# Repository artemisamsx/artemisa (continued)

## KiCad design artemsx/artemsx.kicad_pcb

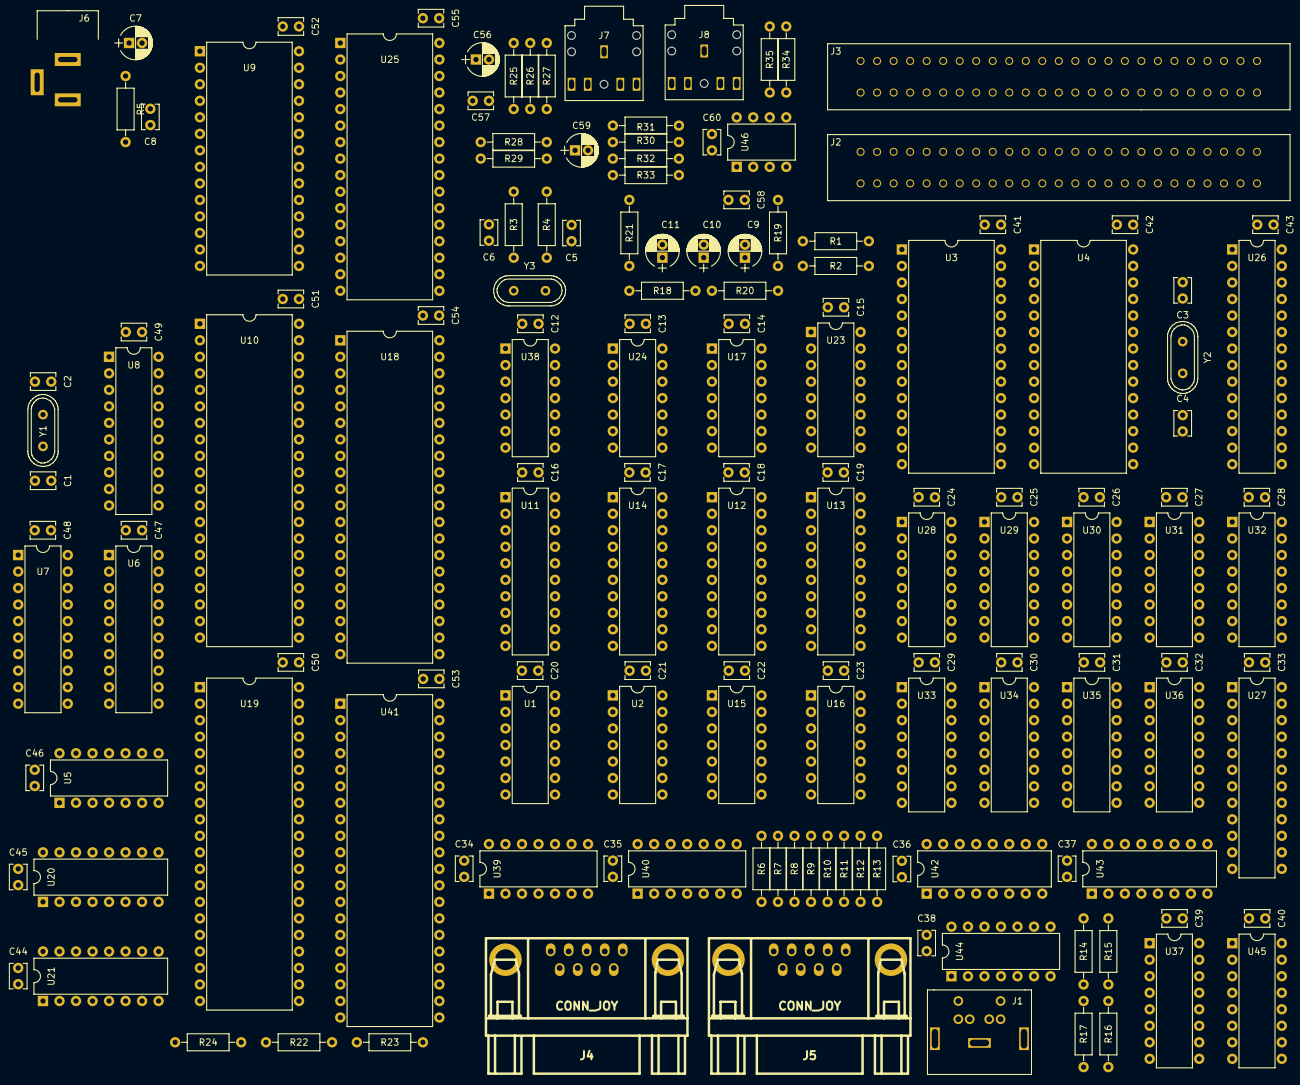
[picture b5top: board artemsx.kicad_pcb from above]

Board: 2 copper layers, 151 parts (0 on the bottom side), 249 nets, no tracks yet.

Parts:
C1, C2: 27pF; Disc_capacitor
C3, C4, C5, C6, C8, C12, C13, C14, C15, C16, C17, C18, C19, C20, C21, C22, C23, C24, C25, C26, C27, C28, C29, C30, C31, C32, C33, C34, C35, C36, C37, C38, C39, C40, C41, C42, C43, C44, C45, C46, C47, C48, C49, C50, C51, C52, C53, C54, C55, C60: 22pF; Disc_capacitor
C7, C56, C59: 1uF; Radial_capacitor
C9, C10, C11: 10u; Radial_capacitor
C57, C58: 22nF; Disc_capacitor
J1: PS2_CONN; PS2_conn
J2, J3: MSX_Slot; Slot_conn
J4, J5: CONN_JOY; Joystick_conn
J6: PWR_conn; Jack_55_21
J7, J8: Audio_conn; Jack_conn
R1, R2, R5, R6, R7, R8, R9, R10, R11, R12, R13, R14, R15, R16, R17, R22, R23, R24: 10K; Axial_resistor
R3: 1M; Axial_resistor
R4: 1K; Axial_resistor
R18: 470; Axial_resistor
R19: 20k; Axial_resistor
R20, R25, R26, R31: 4k7; Axial_resistor
R21, R28, R29: 2k7; Axial_resistor
R27: 100; Axial_resistor
R30, R34: 10k; Axial_resistor
R32: 220k; Axial_resistor
R33: 1k; Axial_resistor
R35: 470k; Axial_resistor
U1, U17, U24, U44: 74HC32; DIP-14_300
U2: 74HC04; DIP-14_300
U3, U4, U9: HM62256ALP-10; DIP-28_600
U5: 74HCT04; DIP-14_300
U6, U7, U8: 74HCT574; DIP-20_300
U10: TMS99x8; DIP-40_600
U11, U12, U14: 74HCT244; DIP-20_300
U13: 74HCT245; DIP-20_300
U15, U40: 74HC74; DIP-14_300
U16: 74HC08; DIP-14_300
U18: Z84C00; DIP-40_600
U19: 82C55A; DIP-40_600
U20: 74HC153; DIP-16_300
U21: 74HC139; DIP-16_300
U23: 74HC138; DIP-16_300
U25: SST39SF0x0; DIP-32_600
U26: ATMEGA328P; DIP-28_300
U27: 74HC154; DIP-24_300
U28, U29, U30, U31, U32, U33, U34, U35, U36, U37, U45: 74HC595; DIP-16_300
U38: 4069; DIP-14_300
U39: 74HC07; DIP-14_300
U41: AY-3-8910; DIP-40_600
U42, U43: 74HC157; DIP-16_300
U46: LM311; DIP-8_300
Y1: 10.7386Mhz; Crystal
Y2: 16Mhz; Crystal
Y3: 3.58Mhz; Crystal

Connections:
/ADDR0: J2.28, J3.28, U3.10, U4.10, U10.13, U11.18, U24.12, U25.12
/ADDR1: J2.27, J3.27, U3.9, U4.9, U11.16, U25.11, U38.13, U44.2
/ADDR3: J2.29, J3.29, U3.7, U4.7, U11.12, U23.1, U25.9
/ADDR4: J2.32, J3.32, U3.6, U4.6, U11.9, U23.2, U25.8
/ADDR5: J2.31, J3.31, U3.5, U4.5, U11.7, U23.3, U25.7
/ADDR6: J2.22, J3.22, U3.4, U4.4, U11.5, U24.2, U25.6
/ADDR7: J2.21, J3.21, U2.9, U3.3, U4.3, U11.3, U25.5
/ADDR14: J2.25, J3.25, U3.1, U4.1, U12.5, U19.9, U20.14, U21.14, U25.29
/ADDR15: J2.18, J3.18, U1.2, U2.1, U12.3, U19.8, U20.2, U21.13, U25.3
/AUDIO: R19.2, R20.2, R21.2
/BEEP: C9.1, U19.10
/CASIN: C58.2, U41.14
/CASOUT: C56.1, U19.12
/CLK: U2.12, U15.3, U15.11, U18.6, U40.3, U44.9, U44.10
/CPU/A0: U11.2, U18.30
/CPU/A1: U11.4, U18.31
/CPU/A2: U11.6, U18.32
/CPU/A3: U11.8, U18.33
/CPU/A4: U11.11, U18.34
/CPU/A5: U11.13, U18.35
/CPU/A6: U11.15, U18.36
/CPU/A7: U11.17, U18.37
/CPU/A8: U12.2, U18.38
/CPU/A9: U12.4, U18.39
/CPU/A10: U12.6, U18.40
/CPU/A11: U12.8, U18.1
/CPU/A12: U12.11, U18.2
/CPU/A13: U12.13, U18.3
/CPU/A14: U12.15, U18.4
/CPU/A15: U12.17, U18.5
/CPU/ADDR2: J2.30, J3.30, U3.8, U4.8, U11.14, U25.10
/CPU/ADDR8: J2.24, J3.24, U3.25, U4.25, U12.18, U25.27
/CPU/ADDR9: J2.17, J3.17, U3.24, U4.24, U12.16, U25.26
/CPU/ADDR10: J2.20, J3.20, U3.21, U4.21, U12.14, U25.23
/CPU/ADDR11: J2.19, J3.19, U3.23, U4.23, U12.12, U25.25
/CPU/ADDR12: J2.23, J3.23, U3.2, U4.2, U12.9, U25.4
/CPU/ADDR13: J2.26, J3.26, U3.26, U4.26, U12.7, U25.28
/CPU/D0: U13.2, U18.14
/CPU/D1: U13.3, U18.15
/CPU/D2: U13.4, U18.12
/CPU/D3: U13.5, U18.8
/CPU/D4: U13.6, U18.7
/CPU/D5: U13.7, U18.9
/CPU/D6: U13.8, U18.10
/CPU/D7: U13.9, U18.13
/CPU/DATA0: J2.34, J3.34, U3.11, U4.11, U10.24, U13.18, U19.34, U25.13, U41.37
/CPU/DATA1: J2.33, J3.33, U3.12, U4.12, U10.23, U13.17, U19.33, U25.14, U41.36
/CPU/DATA2: J2.36, J3.36, U3.13, U4.13, U10.22, U13.16, U19.32, U25.15, U41.35
/CPU/DATA3: J2.35, J3.35, U3.15, U4.15, U10.21, U13.15, U19.31, U25.17, U41.34
/CPU/DATA4: J2.38, J3.38, U3.16, U4.16, U10.20, U13.14, U19.30, U25.18, U41.33
/CPU/DATA5: J2.37, J3.37, U3.17, U4.17, U10.19, U13.13, U19.29, U25.19, U41.32
/CPU/DATA6: J2.40, J3.40, U3.18, U4.18, U10.18, U13.12, U19.28, U25.20, U41.31
/CPU/DATA7: J2.39, J3.39, U3.19, U4.19, U10.17, U13.11, U19.27, U25.21, U41.30
/CPU/~INT: U16.3, U18.16
/KBD/DS: U26.11, U28.14, U29.14, U30.14, U31.14, U32.14, U33.14, U34.14, U35.14, U36.14, U37.14, U45.14
/KBD/KBCOL0: U19.18, U28.15, U29.15, U30.15, U31.15, U32.15, U33.15, U34.15, U35.15, U36.15, U37.15, U45.15
/KBD/KBCOL1: U19.19, U28.1, U29.1, U30.1, U31.1, U32.1, U33.1, U34.1, U35.1, U36.1, U37.1, U45.1
/KBD/KBCOL2: U19.20, U28.2, U29.2, U30.2, U31.2, U32.2, U33.2, U34.2, U35.2, U36.2, U37.2, U45.2
/KBD/KBCOL3: U19.21, U28.3, U29.3, U30.3, U31.3, U32.3, U33.3, U34.3, U35.3, U36.3, U37.3, U45.3
/KBD/KBCOL4: U19.22, U28.4, U29.4, U30.4, U31.4, U32.4, U33.4, U34.4, U35.4, U36.4, U37.4, U45.4
/KBD/KBCOL5: U19.23, U28.5, U29.5, U30.5, U31.5, U32.5, U33.5, U34.5, U35.5, U36.5, U37.5, U45.5
/KBD/KBCOL6: U19.24, U28.6, U29.6, U30.6, U31.6, U32.6, U33.6, U34.6, U35.6, U36.6, U37.6, U45.6
/KBD/KBCOL7: U19.25, U28.7, U29.7, U30.7, U31.7, U32.7, U33.7, U34.7, U35.7, U36.7, U37.7, U45.7
/KBD/KBROW0: U19.14, U27.23
/KBD/KBROW1: U19.15, U27.22
/KBD/KBROW2: U19.16, U27.21
/KBD/KBROW3: U19.17, U27.20
/KBD/SHCP: U26.6, U28.11, U29.11, U30.11, U31.11, U32.11, U33.11, U34.11, U35.11, U36.11, U37.11, U45.11
/KBD/STCP0: U26.23, U28.12
/KBD/STCP1: U26.24, U29.12
/KBD/STCP2: U26.25, U30.12
/KBD/STCP3: U26.26, U31.12
/KBD/STCP4: U26.27, U32.12
/KBD/STCP5: U26.28, U33.12
/KBD/STCP6: U26.14, U34.12
/KBD/STCP7: U26.15, U35.12
/KBD/STCP8: U26.16, U36.12
/KBD/STCP9: U26.17, U37.12
/KBD/STCP10: U26.18, U45.12
/KBD/~RSL0: U27.1, U28.13
/KBD/~RSL1: U27.2, U29.13
/KBD/~RSL2: U27.3, U30.13
/KBD/~RSL3: U27.4, U31.13
/KBD/~RSL4: U27.5, U32.13
/KBD/~RSL5: U27.6, U33.13
/KBD/~RSL6: U27.7, U34.13
/KBD/~RSL7: U27.8, U35.13
/KBD/~RSL8: U27.9, U36.13
/KBD/~RSL9: U27.10, U37.13
/KBD/~RSL10: U27.11, U45.13
/PPI/PA0: U19.4, U20.6
/PPI/PA1: U19.3, U20.10
/PPI/PA2: U19.2, U20.5
/PPI/PA3: U19.1, U20.11
/PPI/PA4: U19.40, U20.4
/PPI/PA5: U19.39, U20.12
/PPI/PA6: U19.38, U20.3
/PPI/PA7: U19.37, U20.13
/PSG/IOA0: U41.21, U42.4
/PSG/IOA1: U41.20, U42.7
/PSG/IOA2: U41.19, U42.9
/PSG/IOA3: U41.18, U42.12
/PSG/IOA4: U41.17, U43.4
/PSG/IOA5: U41.16, U43.7
/PSG/IOB0: U39.1, U41.13
/PSG/IOB1: U39.3, U41.12
/PSG/IOB2: U39.5, U41.11
/PSG/IOB3: U39.9, U41.10
/PSG/IOB4: J4.8, U41.9
/PSG/IOB5: J5.8, U41.8
/PSG/IOB6: U41.7, U42.1, U43.1
/PSG/JOYA1: J4.1, R13.2, U42.2
/PSG/JOYA2: J4.2, R12.2, U42.5
/PSG/JOYA3: J4.3, R11.2, U42.11
/PSG/JOYA4: J4.4, R10.2, U42.14
/PSG/JOYA6: J4.6, R17.1, U39.8, U43.2
/PSG/JOYA7: J4.7, R16.1, U39.6, U43.5
/PSG/JOYB1: J5.1, R9.2, U42.3
/PSG/JOYB2: J5.2, R8.2, U42.6
/PSG/JOYB3: J5.3, R7.2, U42.10
/PSG/JOYB4: J5.4, R6.2, U42.13
/PSG/JOYB6: J5.6, R15.1, U39.4, U43.3
/PSG/JOYB7: J5.7, R14.1, U39.2, U43.6
/SLOTS/EXTCLK: J2.42, J3.42, U44.8
/SLOTS/~EXTRESET: J2.15, J3.15, U44.11
/SOUND: C10.1, J2.49, J3.49
/VDP/AD0: U6.2, U7.2, U8.2, U10.10
/VDP/AD1: U6.3, U7.3, U8.3, U10.9
/VDP/AD2: U6.4, U7.4, U8.4, U10.8
/VDP/AD3: U6.5, U7.5, U8.5, U10.7
/VDP/AD4: U6.6, U7.6, U8.6, U10.6
/VDP/AD5: U6.7, U7.7, U8.7, U10.5
/VDP/AD6: U6.8, U7.8, U8.8, U10.4
/VDP/AD7: U6.9, U7.9, U8.9, U10.3
/VDP/COL: U5.12, U8.11
/VDP/RD: U5.4, U6.1, U9.27
/VDP/ROW: U5.6, U7.11
/VDP/VD0: U6.19, U9.11, U10.32
/VDP/VD1: U6.18, U9.12, U10.31
/VDP/VD2: U6.17, U9.13, U10.30
/VDP/VD3: U6.16, U9.15, U10.29
/VDP/VD4: U6.15, U9.16, U10.28
/VDP/VD5: U6.14, U9.17, U10.27
/VDP/VD6: U6.13, U9.18, U10.26
/VDP/VD7: U6.12, U9.19, U10.25
/VDP/WR: U5.2, U5.3, U6.11, U9.22
/VDP/~CAS: U5.9, U9.20, U10.2
/VDP/~CSR: U1.11, U10.15
/VDP/~CSW: U1.8, U10.14
/VDP/~RAS: U5.5, U10.1
/~CS1: J2.1, J3.1, U16.10, U21.11
/~CS2: J2.2, J3.2, U16.9, U21.10
/~CS12: J2.3, J3.3, U16.8
/~EXTINT: J2.8, J3.8, R1.2, U16.1
/~EXTWAIT: J2.7, J3.7, R2.2, U15.1, U15.10
/~IORQ: J2.11, J3.11, U14.14, U17.1, U23.5
/~IOSL3: U1.10, U1.12, U23.12
/~IOSL4: U23.11, U24.10, U44.1
/~IOSL5: U17.5, U17.9, U23.10, U40.10
/~M1: J2.9, J3.9, U14.18, U15.2, U17.2, U23.6
/~MREQ: J2.12, J3.12, U14.16, U17.12
/~RD: J2.14, J3.14, U1.13, U3.22, U4.22, U14.9, U16.4, U17.4, U21.15, U24.4, U25.24
/~RESET: C8.1, U2.3, U10.34, U18.26, U26.1, U38.4, U40.13, U41.23, U44.12, U44.13
/~RFSH: J2.6, J3.6, U2.5, U14.5
/~SLTSL0: U21.4, U25.22
/~SLTSL1: U1.1, U1.4, U21.5
/~SLTSL2: J2.4, U21.6
/~SLTSL3: J3.4, U21.7
/~VDPINT: U10.16, U16.2
/~WR: J2.13, J3.13, U1.9, U3.27, U4.27, U14.7, U17.10, U44.5
GND: C1.2, C2.2, C3.2, C4.2, C5.2, C6.2, C7.2, C8.2, C12.2, C13.2, C14.2, C15.2, C16.2, C17.2, C18.2, C19.2, C20.2, C21.2, C22.2, C23.2, C24.2, C25.2, C26.2, C27.2, C28.2, C29.2, C30.2, C31.2, C32.2, C33.2, C34.2, C35.2, C36.2, C37.2, C38.2, C39.2, C40.2, C41.2, C42.2, C43.2, C44.2, C45.2, C46.2, C47.2, C48.2, C49.2, C50.2, C51.2, C52.2, C53.2, C54.2, C55.2, C57.2, C59.2, C60.2, J1.3, J2.41, J2.43, J2.48, J2.50, J3.41, J3.43, J3.48, J3.50, J4.9, J5.9, J6.2, J6.3, J7.1, J8.1, R18.2, R22.2, R23.2, R24.1, R27.1, R29.1, U1.7, U2.7, U3.14, U4.14, U5.7, U6.10, U7.1, U7.10, U8.1, U8.10, U9.1, U9.14, U10.12, U11.1, U11.10, U11.19, U12.1, U12.10, U12.19, U13.10, U13.19, U14.1, U14.8, U14.10, U14.17, U14.19, U15.7, U16.7, U17.7, U18.29, U19.6, U19.7, U20.8, U21.8, U23.8, U24.7, U25.1, U25.2, U25.16, U25.30, U26.8, U26.22, U27.12, U27.18, U27.19, U28.8, U29.8, U30.8, U31.8, U32.8, U33.8, U34.8, U35.8, U36.8, U37.8, U38.7, U39.7, U40.7, U40.11, U40.12, U41.1, U41.24, U42.8, U42.15, U43.8, U43.10, U43.11, U43.13, U43.14, U43.15, U44.7, U45.8, U46.1, U46.4
unnamed: C1.1, U10.40, Y1.1
unnamed: C2.1, U10.39, Y1.2
unnamed: C3.1, U26.9, Y2.1
unnamed: C4.1, U26.10, Y2.2
unnamed: C5.1, R4.2, Y3.2
unnamed: C6.1, R3.2, U38.5, Y3.1
unnamed: C7.1, R5.2, U38.1
unnamed: C9.2, R19.1
unnamed: C10.2, R20.1
unnamed: C11.1, R18.1, U41.3, U41.4, U41.38
unnamed: C11.2, R21.1
unnamed: C56.2, R25.2
unnamed: C57.1, R25.1, R26.2
unnamed: C58.1, R34.1
unnamed: C59.1, R28.1, R29.2, R30.2, R31.1
unnamed: J1.1, U26.5
unnamed: J1.5, U26.4
unnamed: J7.2, R26.1, R27.2
unnamed: J8.2, R32.2, R33.1, U46.7
unnamed: R3.1, R4.1, U38.6, U38.9
unnamed: R22.1, U41.6
unnamed: R23.1, U41.15
unnamed: R30.1, R34.2, R35.1, U46.3
unnamed: R31.2, R32.1, U46.2
unnamed: U1.3, U3.20
unnamed: U1.5, U2.2
unnamed: U1.6, U4.20
unnamed: U2.8, U24.1
unnamed: U2.10, U41.29
unnamed: U2.13, U38.8
unnamed: U5.10, U5.13
unnamed: U5.8, U5.11
unnamed: U7.12, U9.4
unnamed: U7.13, U9.5
unnamed: U7.14, U9.6
unnamed: U7.15, U9.7
unnamed: U7.16, U9.8
unnamed: U7.17, U9.9
unnamed: U7.18, U9.10
unnamed: U8.12, U9.26
unnamed: U8.13, U9.2
unnamed: U8.14, U9.23
unnamed: U8.15, U9.21
unnamed: U8.16, U9.24
unnamed: U8.17, U9.25
unnamed: U8.18, U9.3
unnamed: U5.1, U10.11
unnamed: U13.1, U16.6
unnamed: U14.2, U18.27
unnamed: U14.4, U18.19
unnamed: U14.6, U18.20
unnamed: U14.11, U18.21
unnamed: U14.13, U18.22
unnamed: U14.15, U18.28
unnamed: U15.4, U15.9
unnamed: U15.5, U15.12, U18.24
unnamed: U16.5, U17.3
unnamed: U2.11, U16.11
unnamed: U16.12, U24.8
unnamed: U16.13, U24.11
unnamed: U17.6, U19.5
unnamed: U17.8, U19.36
unnamed: U17.11, U21.1
unnamed: U2.6, U17.13
unnamed: U2.4, U19.35
unnamed: U20.1, U20.15, U40.8
unnamed: U20.7, U21.2
unnamed: U20.9, U21.3
unnamed: U23.4, U24.3
unnamed: U24.5, U38.12
unnamed: U24.6, U24.9
unnamed: U24.13, U38.11, U44.6
unnamed: U38.2, U38.3
unnamed: U38.10, U41.27
unnamed: U40.2, U40.6
unnamed: U40.5, U41.22
unnamed: U44.3, U44.4
VCC: C12.1, C13.1, C14.1, C15.1, C16.1, C17.1, C18.1, C19.1, C20.1, C21.1, C22.1, C23.1, C24.1, C25.1, C26.1, C27.1, C28.1, C29.1, C30.1, C31.1, C32.1, C33.1, C34.1, C35.1, C36.1, C37.1, C38.1, C39.1, C40.1, C41.1, C42.1, C43.1, C44.1, C45.1, C46.1, C47.1, C48.1, C49.1, C50.1, C51.1, C52.1, C53.1, C54.1, C55.1, C60.1, J1.4, J2.45, J2.47, J3.45, J3.47, J4.5, J5.5, J6.1, R1.1, R2.1, R5.1, R6.1, R7.1, R8.1, R9.1, R10.1, R11.1, R12.1, R13.1, R14.2, R15.2, R16.2, R17.2, R28.2, R33.2, R35.2, U1.14, U2.14, U3.28, U4.28, U5.14, U6.20, U7.20, U8.20, U9.28, U10.33, U11.20, U12.20, U13.20, U14.20, U15.13, U15.14, U16.14, U17.14, U18.11, U18.17, U18.25, U19.26, U20.16, U21.16, U23.16, U24.14, U25.31, U25.32, U26.7, U26.20, U26.21, U27.24, U28.10, U28.16, U29.10, U29.16, U30.10, U30.16, U31.10, U31.16, U32.10, U32.16, U33.10, U33.16, U34.10, U34.16, U35.10, U35.16, U36.10, U36.16, U37.10, U37.16, U38.14, U39.11, U39.13, U39.14, U40.1, U40.4, U40.14, U41.25, U41.28, U41.40, U42.16, U43.16, U44.14, U45.10, U45.16, U46.8

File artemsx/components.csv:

Ref,Type,Sheet
U1A,74HC32,RAM
U1B,74HC32,RAM
U1C,74HC32,VDP
U1D,74HC32,VDP
U2A,74HC04,RAM
U2B,74HC04,PPI
U2C,74HC04,PPI
U2D,74HC04,IO
U2E,74HC04,PSG
U2F,74HC04,---
U3,HM62256ALP-10,RAM
U4,HM62256ALP-10,RAM
U5A,74HCT04,VDP
U5B,74HCT04,VDP
U5C,74HCT04,VDP
U5D,74HCT04,VDP
U5E,74HCT04,VDP
U5F,74HCT04,VDP
U6,74HCT574,VDP
U7,74HCT574,VDP
U8,74HCT574,VDP
U9,HM62256ALP-10,VDP
U10,TMS99x8,VDP
U11A,74HCT244,CPU
U11B,74HCT244,CPU
U12A,74HCT244,CPU
U12B,74HCT244,CPU
U13,74HCT245,CPU
U14A,74HCT244,CPU
U14B,74HCT244,CPU
U15A,74HC74,CPU
U15B,74HC74,CPU
U16A,74HC08,CPU
U16B,74HC08,CPU
U16C,74HC08,PPI
U16D,74HC08,PSG
U17A,74HC32,CPU
U17B,74HC32,PPI
U17C,74HC32,PPI
U17D,74HC32,PPI
U18,Z84C006,CPU
U19,82C55A,PPI
U20,74HC153,PPI
U21A,74HC139,PPI
U21B,74HC139,PPI
U23,74HC138,IO
U24A,74HC32,IO
U24B,74HC32,PSG
U24C,74HC32,PSG
U24D,74HC32,PSG
U25,SST39SF0x0,ROM
U26,ATMEGA328P,KBD
U27,74HC154,KBD
U28,74HC595,KBD
U29,74HC595,KBD
U30,74HC595,KBD
U31,74HC595,KBD
U32,74HC595,KBD
U33,74HC595,KBD
U34,74HC595,KBD
U35,74HC595,KBD
U36,74HC595,KBD
U37,74HC595,KBD
U38A,4069,CPU
U38B,4069,CPU
U38C,4069,CPU
U38D,4069,CPU
U38E,4069,PSG
U38F,4069,PSG
U39A,74HC07,PSG
U39B,74HC07,PSG
U39C,74HC07,PSG
U39D,74HC07,PSG
U39E,74HC07,PSG*
U39F,74HC07,PSG*
U40A,74HC74,PSG
U40B,74HC74,PPI
U41,AY-3-8910,PSG
U42,74HC157,PSG
U43,74HC157,PSG
U44A,74HC32,PSG
U44B,74HC32,PSG
U44C,74HC32,SLOTS
U44D,74HC32,SLOTS
U45,74HC595,KBD
U46,LM311,CAS
Y1,10.7386,VDP
Y2,16MHZ,KBD
Y3,3.58MHZ,CPU
R1,10K,SLOTS
R2,10K,SLOTS
R3,1M,CPU
R4,1K,CPU
R5,10K,CPU
R6,10K,PSG
R7,10K,PSG
R8,10K,PSG
R9,10K,PSG
R10,10K,PSG
R11,10K,PSG
R12,10K,PSG
R13,10K,PSG
R14,10K,PSG
R15,10K,PSG
R16,10K,PSG
R17,10K,PSG
R18,470,PSG
R19,20k,PSG
R20,4k7,PSG
R21,2k7,PSG
R22,10K,PSG
R23,10K,PSG
R24,10K,PSG
R25,4k7,CAS
R26,4k7,CAS
R27,100,CAS
R28,2k7,CAS
R29,2k7,CAS
R30,10k,CAS
R31,4k7,CAS
R32,220k,CAS
R33,1k,CAS
R34,10k,CAS
R35,470k,CAS
J1,PS2CONN,KBD
J2,MSXSLOT,SLOTS
J3,MSXSLOT,SLOTS
J4,JOYCONN,PSG
J5,JOYCONN,PSG
J6,PWRCONN,PWR
J7,AUDIOCONN,CAS
J8,AUDIOCONN,CAS
C1,27pF,VDP
C2,27pF,VDP
C3,22pF,KBD
C4,22pF,KBD
C5,22pF,CPU
C6,22pF,CPU
C7,1uF,CPU
C8,22pF,CPU
C9,10uF,PSG
C10,10uF,PSG
C11,10uF,PSG
C12,22pF,PWR
C13,22pF,PWR
C14,22pF,PWR
C15,22pF,PWR
C16,22pF,PWR
C17,22pF,PWR
C18,22pF,PWR
C19,22pF,PWR
C20,22pF,PWR
C21,22pF,PWR
C22,22pF,PWR
C23,22pF,PWR
C24,22pF,PWR
C25,22pF,PWR
C26,22pF,PWR
C27,22pF,PWR
C28,22pF,PWR
C29,22pF,PWR
C30,22pF,PWR
C31,22pF,PWR
C32,22pF,PWR
C33,22pF,PWR
C34,22pF,PWR
C35,22pF,PWR
C36,22pF,PWR
C37,22pF,PWR
C38,22pF,PWR
C39,22pF,PWR
C40,22pF,PWR
C41,22pF,PWR
C42,22pF,PWR
C43,22pF,PWR
C44,22pF,PWR
C45,22pF,PWR
C46,22pF,PWR
C47,22pF,PWR
C48,22pF,PWR
C49,22pF,PWR
C50,22pF,PWR
C51,22pF,PWR
C52,22pF,PWR
C53,22pF,PWR
C54,22pF,PWR
C55,22pF,PWR
C56,1uF,CAS
C57,22nF,CAS
C58,22nF,CAS
C59,1uF,CAS

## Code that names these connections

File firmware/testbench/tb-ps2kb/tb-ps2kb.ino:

// Artemisa Computer System
// PS2 Keyboard Adapter Testbench
// Copyright (C) 2018-2019 Alvaro Polo
//
// This is an Arduino sketch aimed to provide a testbench for the PS2 Keyboard
// Adapter board. It basically makes the Arduino simulate an Artemisa Computer
// motherboard, interacting with the adapter board as it were a real keyboard
// matrix.
//
// It works for Arduino Mega or Arduino Mega 2560 boards only.

// A flag used for deep debugging
#define DEBUG 0

// The baud rate used for the serial communication
#define SERIAL_BAUDRATE 9600

// The number of rows present in the keyboard matrix
#define NROWS     11

// The number of columns present in the keyboard matrix
#define NCOLS     8

// Pin settings for KBCOL bus lines
#define PIN_KBCOL0 2
#define PIN_KBCOL1 3
#define PIN_KBCOL2 4
#define PIN_KBCOL3 5
#define PIN_KBCOL4 6
#define PIN_KBCOL5 7
#define PIN_KBCOL6 8
#define PIN_KBCOL7 9

// Pin settings for RSL bus lines
#define PIN_RSL0    22
#define PIN_RSL1    23
#define PIN_RSL2    24
#define PIN_RSL3    25
#define PIN_RSL4    26
#define PIN_RSL5    27
#define PIN_RSL6    28
#define PIN_RSL7    29
#define PIN_RSL8    30
#define PIN_RSL9    31
#define PIN_RSL10   32

#define PIN_CAPSLOCK  11
#define PIN_KANALOCK  12
#define PIN_RESET     13


// The pins used by KBCOL bus lines
const int pins_kbcol[NCOLS] = {
  PIN_KBCOL0, PIN_KBCOL1, PIN_KBCOL2, PIN_KBCOL3,
  PIN_KBCOL4, PIN_KBCOL5, PIN_KBCOL6, PIN_KBCOL7,
};

// The pins used by RSL bus lines
const int pins_rsl[NROWS] = {
  PIN_RSL0, PIN_RSL1, PIN_RSL2, PIN_RSL3, PIN_RSL4, PIN_RSL5,
  PIN_RSL6, PIN_RSL7, PIN_RSL8, PIN_RSL9, PIN_RSL10,
};

// Setup of Arduino pins
void setupPins() {
  for (int i = 0; i < NCOLS; i++) {
    pinMode(pins_kbcol[i], INPUT_PULLUP);
  }
  for (int i = 0; i < NROWS; i++) {
    pinMode(pins_rsl[i], OUTPUT);
    digitalWrite(pins_rsl[i], HIGH); // Reverse logic
  }
  pinMode(PIN_CAPSLOCK, OUTPUT);
  pinMode(PIN_KANALOCK, OUTPUT);
  pinMode(PIN_RESET, OUTPUT);
  digitalWrite(PIN_CAPSLOCK, HIGH); // Reverse logic
  digitalWrite(PIN_KANALOCK, HIGH); // Reverse logic
  digitalWrite(PIN_RESET, HIGH); // Reverse logic
}

// Reset the PS2 Adapter board
void reset() {
  digitalWrite(PIN_RESET, LOW);
  delay(50);
  digitalWrite(PIN_RESET, HIGH);
}

// Deselect the row from the keyboard matrix
void deselectRow() {
  for (int i = 0; i < NROWS; i++) {
    digitalWrite(pins_rsl[i], HIGH);
  }
}

// Select the given row of the keyboard matrix
void selectRow(unsigned int row) {
  if (row > NROWS) {
    return;
  }
  deselectRow();
  digitalWrite(pins_rsl[row], LOW);
}

// Read the columns from the selected row
byte readRow() {
  byte col = 0;
  for (int i = 7; i >= 0; i--) {
    col <<= 1;
    col |= digitalRead(pins_kbcol[i]);
  }
  return col;
}

// Setup of the serial port
void setupSerial() {
  Serial.begin(SERIAL_BAUDRATE);
  Serial.println("PS2 Keyboard Adapter initialized");
}

// Setup the Arduino board
void setup() {
  setupPins();
  reset();
  setupSerial();
}

// The current known status of the matrix
static byte matrix_status[] = {
  0xff, 0xff, 0xff, 0xff, 0xff, 0xff, 0xff, 0xff, 0xff, 0xff, 0xff
};

// The current status of the caps lock
static bool capslock_status = false;

// The mapping from keys to symbols with lower case
const char mappingLower[] = {
  '0', '1', '2', '3', '4', '5', '6', '7',
  '8', '9', '-', '=', '\\', '[', ']', ';',
  '\'', '`', ',', '.', '/', ' ', 'a', 'b',
  'c', 'd', 'e', 'f', 'g', 'h', 'i', 'j',
  'k', 'l', 'm', 'n', 'o', 'p', 'q', 'r',
  's', 't', 'u', 'v', 'w', 'x', 'y', 'z',
};

// The mapping from keys to symbols with upper case
const char mappingUpper[] = {
  ')', '!', '@', '#', '$', '%', '^', '&',
  '*', '(', '_', '+', '|', '{', '}', ':',
  '"', '~', '<', '>', '?', ' ', 'A', 'B',
  'C', 'D', 'E', 'F', 'G', 'H', 'I', 'J',
  'K', 'L', 'M', 'N', 'O', 'P', 'Q', 'R',
  'S', 'T', 'U', 'V', 'W', 'X', 'Y', 'Z',
};

// The mapping from keys to symbols for the keypad
const char mappingKeypad[] = {
  '*', '+', '/', '0', '1', '2', '3', '4',
  '5', '6', '7', '8', '9', '-', ',', '.',
};

void processKey(unsigned int row, byte before, byte after) {
  for (int i = 0; i < NCOLS; i++) {
    if ((before & 1) == 0 && (after & 1) == 1) {
      // Key released
      if (row == 8 && i == 0) {
        // Space bar
        Serial.print(" ");
      } else if (row == 7 && i == 7) {
        // Return
        Serial.println("");
      } else if (row == 6 && i == 3) {
        // Caps lock
        capslock_status = !capslock_status;
        digitalWrite(PIN_CAPSLOCK, capslock_status ? LOW : HIGH);
      } else if (row < 6 && !(row == 2 && i == 5)) {
        // Regular key (other than DEAD)
        if (capslock_status) {
          Serial.print(mappingUpper[row * NCOLS + i]);
        } else {
          Serial.print(mappingLower[row * NCOLS + i]);
        }
      } else if (row >= 9) {
        // Keypad
        Serial.print(mappingKeypad[(row - 9) * NCOLS + i]);
      } else {
        // Unknown. Print coordinates
        Serial.print("<");
        Serial.print(row);
        Serial.print(";");
        Serial.print(i);
        Serial.print(">");
      }

    }
    before >>= 1;
    after >>= 1;
  }
}

// Main program
void loop() {
  for (int i = 0; i < NROWS; i++) {
    selectRow(i);
    byte row = readRow();
    if (matrix_status[i] != row) {
#if DEBUG == 1
      Serial.print("Detected changes in row ");
      Serial.print(i);
      Serial.print(": ");
      Serial.print(row, BIN);
      Serial.println("");
#endif

      processKey(i, matrix_status[i], row);
      matrix_status[i] = row;
    }
  }
}

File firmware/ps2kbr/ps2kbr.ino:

// Artemisa Computer System
// PS2 keyboard matrix emulator
// Copyright (C) 2018-2019 Alvaro Polo
//
// This is an Arduino sketch that implements the firmware of the keyboard
// matrix emulator used in the Artemisa Computer System. The purpose of
// this firmware is to adapt the PS2 interface of a modern keyboard and
// expose it to the MSX as a old-school keyboard matrix.
//
// It does so by using a network of 74HC595 ICs connected to an ATmega328
// microcontroller. The 595 network will operate as a sort of small and
// unexpensive dual-port memory based upon serial-to-parallel shift registers.
// The ATmega will write bytes into it using the serial interface (write port),
// while the MSX PPI will read the bytes using the parallel interface (read
// port). Each 595 stores 8-bits, representing a single row of the MSX keyboard
// matrix. Using a total of eleven 595s you can represent the whole keyboard
// matrix.
//

// This macro, when declared, activates the debug mode using the serial port of the Arduino board.
// There is another PS2_DEBUG macro that controls the low level debugging in the PS2 library.
// You can comment and uncomment this to disable and enable debug, respectively.
// #define DEBUG 1

// The custom PS2 library made by Artemisa project.
#include "ps2.h"

// The mappings between PS2 scancodes and MSX matrix positions
#include "mapping.h"

// The Arduino pin where PS2 DATA is connected.
#define PS2_PIN_DATA     3 // ATmega328 pin #5 (PD3/INT1)

// The Arduino pin where PS2 CLOCK is connected.
// Note: this MUST be connected to an interrupt pin.
#define PS2_PIN_CLK      2 // ATmega328 pin #4 (PD2/INT0)

// The Arduino pin where matrix DS line is connected.
#define MATRIX_PIN_DS    5 // ATmega328 pin #11 (PD5)

// The Arduino pin where matrix SHCP line is connected.
#define MATRIX_PIN_SHCP  4 // ATmega328 pin #6 (PD4)

// The Arduino pin where CAPSLOCK line is connected.
#define KANALOCK_PIN     6 // ATmega328 pin #12 (PD6)

// The Arduino pin where CAPSLOCK line is connected.
#define CAPSLOCK_PIN     13 // ATmega328 pin #19 (PB5/SCLK)

// How many rows of MSX matrix we will emulate
#define MATRIX_NROWS     11

// What is the maximum scancode from PS2 keyboard we will process
#define KEYCODE_MAX      0xa0

// An array that indicates the Arduino pins where each matrix row STCP signal
// is connected.
const int outputs[MATRIX_NROWS] = {
  A0, // STCP0, ATmega328 pin #23 (PC0)
  A1, // STCP1, ATmega328 pin #24 (PC1)
  A2, // STCP2, ATmega328 pin #25 (PC2)
  A3, // STCP3, ATmega328 pin #26 (PC3)
  A4, // STCP4, ATmega328 pin #27 (PC4)
  A5, // STCP5, ATmega328 pin #28 (PC5)
  8,  // STCP6, ATmega328 pin #14 (PB0)
  9,  // STCP7, ATmega328 pin #15 (PB1)
  10, // STCP8, ATmega328 pin #16 (PB2/SS)
  11, // STCP9, ATmega328 pin #17 (PB3/MOSI)
  12, // STCP10, ATmega328 pin #18 (PB4/MISO)
};

// An array that maintains the state of the MSX matrix.
// Each item represents the n-th row of the matrix. Each row has 8 columns,
// each one represented by one bit in each entry of this array.
byte matrix[MATRIX_NROWS];

// The PS2 port
PS2Port ps2;

// Initialize the IO pins
void init_iopins() {
  // The pin used to transmit the serial data
  pinMode(MATRIX_PIN_DS, OUTPUT);
  digitalWrite(MATRIX_PIN_DS, 0);

  // The pin used to transmit shift clock.
  pinMode(MATRIX_PIN_SHCP, OUTPUT);
  digitalWrite(MATRIX_PIN_SHCP, 0);

  // The pins used to transmit storage register clock to each 595.
  for (int i = 0; i < MATRIX_NROWS; i++) {
    pinMode(outputs[i], OUTPUT);
    digitalWrite(outputs[i], LOW);
  }

  // The pins used to read CAPSLOCK and KANALOCK signals
  pinMode(CAPSLOCK_PIN, INPUT_PULLUP);
  pinMode(KANALOCK_PIN, INPUT_PULLUP);
}

// Initialize the matrix
void init_matrix() {
  byte value = 0xff; // all 1s means unpressed
  for (int i = 0; i < MATRIX_NROWS; i++) {
    matrix[i] = value;
  }
  write_all_rows(value);
}

// Shift the given value to all 595s.
// Note this just shifts the value. It will not latch it.
void shift_value(byte value) {
  shiftOut(MATRIX_PIN_DS, MATRIX_PIN_SHCP, MSBFIRST, value);
}

// Latch the previously shifted value to 595 that governs the given row.
void latch_row(int row) {
  digitalWrite(outputs[row], HIGH);
  delayMicroseconds(10);
  digitalWrite(outputs[row], LOW);
}

// Write the given value for the given row.
// This shifts the value and sends the latch signal to the 595 that governs
// that row.
void write_row(int row, byte value) {
  shift_value(value);
  latch_row(row);
}

// Write the given value to all rows
void write_all_rows(byte value) {
  // We want each 595 to be loaded with value. To do that, we shift it to all
  // registers and then we send a latch signal to each 595.
  shift_value(value);
  for (int i = 0; i < MATRIX_NROWS; i++) {
    latch_row(i);
  }
}

void reset_keyboard() {
  PS2Result err = ps2.send_cmd_reset();
  if (err != PS2Result::OK) {
#ifdef DEBUG
    Serial.print(F("Error: reset command failed with code "));
    Serial.println(err, HEX);
#endif
  }
}

void setup_ps2_keyboard() {
  ps2.begin(PS2_PIN_DATA, PS2_PIN_CLK);
  reset_keyboard();
}

void process_locks(bool force = false) {
  static uint8_t locks = 0;

  uint8_t prev = locks;
  if (digitalRead(CAPSLOCK_PIN)) locks &= ~PS2_LED_CAPSLOCK;
  else locks |= PS2_LED_CAPSLOCK;

  // TODO: not all keyboards support Kana Lock LED and refuse this bit.
  // if (digitalRead(KANALOCK_PIN)) locks &= ~PS2_LED_KANALOCK;
  // else locks |= PS2_LED_KANALOCK;

  if (force || (prev != locks)) {
    ps2.send_cmd_leds(locks);
  }
}

bool handle_special_scancode(const PS2Scancode &sc) {
  switch (sc.keycode()) {
    case PS2_KEYCODE_SELFTEST_PASSED:
      process_locks(true);
      return true;
  }
  return false;
}

void handle_scancode(const PS2Scancode &sc) {
  if (handle_special_scancode(sc)) {
    return;
  }

  mapping m = map_scancodes(sc);
  if (m.row == -1) {
    // There is no mapping defined for that scancode. Skip it.
    return;
  }

  byte r = matrix[m.row];
  if (sc.is_break()) {
    bitSet(r, m.offset);
  } else {
    bitClear(r, m.offset);
  }

  if (r != matrix[m.row]) {
    // We detected a change in the row. Something was pressed or released!
#ifdef DEBUG
    //Serial.print(F("Row changed: "));
    //Serial.print(m.row);
    //Serial.print(F("="));
    //Serial.println(r, BIN);
#endif
    matrix[m.row] = r;
    write_row(m.row, r);
  }
}

void process_scancodes() {
  PS2Scancode sc;
  PS2Result res = ps2.receive_scancode(sc);
  if (res != PS2Result::OK) {
#ifdef DEBUG
    Serial.print(F("+RCVERR:"));
    Serial.println(res, HEX);
    return;
#endif
  }
  if (!sc.is_null()) {
    handle_scancode(sc);
  }
}

// Setup the microcontroller
void setup() {
#ifdef DEBUG
  Serial.begin(57600);
  Serial.println( F( "PS2 Keyboard Adapter board" ) );
#endif

  setup_ps2_keyboard();
  init_iopins();
  init_matrix();
}

// Main loop of the microcontroller
void loop() {
  process_scancodes();
  process_locks();
}

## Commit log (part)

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2018-11-26 Update components list
2018-11-26 Move IO device selection signal decoding to DECODING sheet
2018-11-27 Move PPIRDY decoding logic to DECODING sheet
2018-11-27 Better arrangement of schematic's root sheet
2018-12-12 Cleanup of bus lines in root sheet
2019-01-02 Add simulation of redesign of CASIN processing
    Simpler design.
2019-01-02 Update casin signal processing in schematics
2019-01-02 Update casin signal processing in PCB
2019-01-12 Add a DIN8 connector to the footprint library
2019-01-12 Fix wrong position of pads in DIN8 component
2019-01-12 Use DIN8 connector for cassette in schematics
2019-01-12 Document how data cassette interface works
2019-03-18 Add gerber directory to gitignore
2019-03-18 Re-arrange the cassette IO circuit to clarify voltage dividers intention
2019-03-18 Fix documentation
2019-03-23 Fix power pin arrangement for NOT and AND gates in motherboard
2019-03-23 Fix power in arrangement for 74HC08
2019-03-23 Fix power pin arrangement for 74HC139
2019-03-24 Fix power pin arrangement for 74HC245
2019-03-24 Fix power in arrangement for 74HC07
2019-03-24 Fix ower pin arrangement for 74HC138
2019-03-24 Fix power pin arrangement for 74HC74
2019-03-24 Fix power pin arrangement for PPI
2019-03-24 Fix power pin arrangement for 74HC595
2019-03-24 Fix power pin arrangement for 74HC154
2019-03-24 Fix power pin arrangement for 74HC11
2019-03-24 Some fixes in power arrangement
2019-03-24 Fix power pin arrangement for PSG
2019-03-24 Fix power pin arrangement for 74HC157
2019-03-24 Fix power pin arrangement for RAM
2019-03-24 Fix power pin arrangement for LM311
2019-03-24 Fix power pin arrangement for Z80
2019-03-25 Fix missing footprint 3D models
    Even add a custom one for the MSX slot connector.
2019-04-03 Replace 4069 by 74HCU04
    The 4069 has a really large response time. This causes a really ugly clock signal when used in the crystal circuit. 74HCU04 is also a unbuffered inverter, and therefore can be used also for crystal c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
2019-04-08 Replace some pull-up resistors by resistor networks
    Prior to add more pull-up resitors, we realised we were using regular
    resistors instead of resistor networks. This change introduces the
    use of networks by:
    - Defining schematic symbols for networks of 4, 6 and 8 resistors
    - Add the corresponding PCB footprints and 3D models
    - Replace the regular resistors by networks
2019-04-10 Add pull-up resistors for KBCOL bus
    This is needed because the KBROW might be selecting a unexisting row. In such case, none of the 595s will be selected, and the bus will be floating.
2019-04-15 Add a LED to CAS Motor output to the schematic
2019-04-15 Add TO92 footprints to the library
2019-04-15 Add cas. motor LED circuit to the PCB
2019-04-15 Add a female DB25 connector symbol to the library
2019-04-15 Add schematic for keyboard PS2 adapter project
2019-04-15 Add footprints for DB25 connectors
2019-04-15 Add PCB design for PS2 Keyboard Adapter
2019-04-17 Add pins for optional pin header in DB25 footprints
    We might want to use an internal connection to a pin header of 100millis instead of the DB25 connector. So we have included additional pins to sold such pin header instead of DB25 header.
2019-04-17 Replace keyboard matrix emulation in motherboard schematic
    Bye, bye, emulator.
2019-04-17 Add KANALOCK signals to keyboard connectors
    Still not used from the motherboard (wired to 5v).
2019-04-17 Replace keyboard matrix emulation in motherboard PCB
2019-04-20 Add an alternative layout for a smaller motherboard
2019-04-21 Fix DB25 connector of keyboard PS2 PCB
    So it stands out from the board.
2019-04-28 Add a testbench Arduino firmware for GFX9918
2019-04-30 Reset annotations in the motherboard
    So we stop having gaps in the IDs. Also, remove the `components.csv` file, hard to keep updated and susceptible to be autogenerated.
2019-05-07 Fix board dimensions and plot rev01 of motherboard
2019-05-12 Assembly code for Artemisa Diagnosis Tool
    An initial version of the tool that performs some checks on the PPI.
2019-05-21 Add the skeleton of Service Manual
2019-05-21 Adapt README for the new docs
2019-05-21 Shorten the DB25 footprints
2019-05-21 Shorten the PCB and the DB25 connector in PS2 Adapter
2019-05-21 Move the DB9 connectors of Motherboard outer
2019-05-21 Move the power DC connector of Motherboard outer
2019-05-22 Configure CNAME file
2019-05-22 Create CNAME
2019-05-22 Generate manuals with Gitbook
2019-05-26 Rename files of GFX9918 testbench
    So they reflect this is a testbench in the sketch name.
2019-05-27 Fix broken code due to PROGMEM in ps2kbr firmware
2019-05-29 Fix wrong debugging message
2019-05-29 Format PS2KeyAdvanced.cpp file
    So we can understand the code.
2019-05-29 Patch PS2KeyAdvanced to server our purposes
    Do not try to interpret the scan codes and map them to high level events. We do not need that, and it is actually preventing things like appropriate caps lock handling.
2019-06-09 Add a new ROM just for test a infinite nop loop
2019-06-14 Fix power-on reset circuit
    Following the same design as in the Philips VG8020.
2019-06-14 Fix sizes of 1N4448 diode symbols
2019-06-14 Add a footprint for an axial diode to the library
2019-06-14 Fix misplaced silkscreen legends
    And fix also some sizes
2019-06-14 Use 74LS07 for U16 instead of CMOS version
2019-06-14 Rename memory symbols
2019-06-20 Hardcode JP keyboard layout to JIS
    By pulling-up the IOA6 pin of the PSG.
2019-07-02 Fix wrong slot connector placement
    The pinout was reversed, and they were placed in such a way that screw separators cannot be inserted.
2019-07-03 Add a relay symbol to the library
2019-07-03 Add relay footprint to the library
2019-07-03 Fix wrong label sizes in diode footprints
2019-07-04 Add a new symbol for PNP transistors
2019-07-04 Fix label sizes for NPN and PNP symbols
2019-07-04 Use 2.2K instead of 4.7K in R13
    4.7 is too large, and it will not saturate Q2.
2019-07-04 Remove part name in Q1 footprint
2019-07-04 Add a jumper symbol to the library
2019-07-04 Add a Jumper footprint to the library
2019-07-04 Drive the /KANALOCK signal from the PSG GPIO port
2019-07-04 Add a push button symbol to the library
2019-07-04 Add a push button footprint to the library
2019-07-05 Add a label for reset button
2019-07-11 Bump Motherboard Mk.I version to rev3
2019-07-15 Honour Kana lock signal
2019-07-15 Increase width of power tracks in GFX9918
2019-08-12 Replace 74HC154 by a pair of 74HC138
2019-08-14 Add missing changes from issues/104
2019-08-14 Change the value of C7 from 47uF to 100uF
2019-08-14 Replace 7411 by 7408 for U18 in schematic
2019-08-14 Rearrange connections from U18 to RN3
    So the pins are aligned in the PCB
2019-08-14 Replace 7411 by 7408 for U18 in PCB
2019-08-14 Fix wrong text sizes in power schematic
2019-08-19 Make changes to the burner script to use eraseall command
2019-08-19 Add a sanity check step at the end of burn action
2019-08-19 Add the MSX-System ROM files
2019-08-20 Fix wrong mapping of some symbol keys
2019-09-02 [ps2-adapter] Add 2 jumpers for KB layout selection
2019-09-02 [ps2-adapter] Add changelog file
2019-09-02 [gfx9918] Bump to rev 3
2019-09-04 [ps2-adapter] Fix capacitor values for clock circuit
2019-09-04 [gfx9918] Fix missing symbol HM62256
2019-09-04 [gfx9918] Fix capacitor values for clock circuit
2019-09-05 [ps2-adapter] Set board settings to match JCLPCB design rules
2019-09-05 [motherboard] Set board settings to match JCLPCB design rules
2019-09-05 Update changelogs and revision numbers of all PCBs
2019-09-05 Fix changelog files to reflect unreleased changes
2019-09-10 [motherboard] Move some PCB elements to make room to slots
2019-09-10 [motherboard] Update changelog
2019-09-10 [motherboard] Fix wrong annular ring size of cartridge slot connectors
2019-09-10 [ps2-adapter] Modify base case file to include both sides
2019-09-10 [motherboard] Add DXF file for case cutting
2019-09-11 [motherboard] Make right corners of the PCB rounded
2019-09-11 [ps2-adapter] Fix dimensions of case to fit PCB
2019-09-12 [ps2-keyboard] Make the PCB corners rounded
2019-09-12 [motherboard] Fix outdated CHANGELOG
2019-09-12 Release artemisa-mk1_rev3
2019-09-14 Add combined case designs
    A combined design includes motherboard and PS2 adapter designs in the same DXF so they are laser cutted togheter.
2019-09-30 [ps2kbr] Add build scripts, instructions and changelog for the firmware
2019-09-30 Some fixes in the cases
2019-09-30 [gfx9920] Use 9928 instead of 9918
2019-09-30 [gfx9920] Introduce LM1881
2019-10-06 Remove the CNAME from this repo (we will use artemisa-website instead)
2019-10-24 Use minipro to burn ROM images in SST39SF chips
2019-11-11 Fix background color issues by unconnecting EXTVDP pin
2019-11-15 Prepare the ground for a rewrite of ps2kbr firmware
2019-11-24 Provide a custom PS2 implementation
2019-11-24 Introduce a document to list the limitations of the Artemisa Computer
    Including the just revealed issue with the cursor up + cursor left + spacebar in the PS2 Keyboard adapter. Also includes a mention to the system reset issues.
2019-11-24 Remove the remains of PS2KeyAdvanced lib
2019-11-24 Update the Changelog
2019-11-24 Remove old code
2019-12-09 Implement a mechanism to detect keyboard reconnection
2019-12-09 Make it more resilient to parity errors
2019-12-09 Fix missing mapping of keypad enter key
2020-01-15 Reduce the speed of serial comms
    When using prototype wires, this causes some rx errors.
2020-03-02 Add buffers for comms received from keyboard
    It seems we cannot inhibit the comms, because this causes buffer overrun
    errors in the device. With this change, the microcontroller uses a
    ring buffer to store already processed scancodes. And the application
    layer reads from there.
2020-03-02 Fix permissions of WRL files
2020-03-07 Fix some timing issues of PS2 protocol
2020-03-10 Reorganize command processing
2020-03-11 Replace command structs by a simple buffer
2020-05-17 Reorganize GFX9918 into sheets
2020-05-17 Rename motherboard project to model 101
2020-05-18 Remove buffers from address and control bus
2020-05-18 Assume open-drain outputs in INT and WAIT signals
2020-05-18 Add footprints for PLCC32 and PLCC44
2020-05-18 Reassociate footprint of ROM to PLCC32
2020-05-18 Use PLCC44 version of Z84 CPU
2020-05-19 Update outdated attributions of 3D shapes
2020-05-19 Add a library component for AS6C1008
2020-05-19 Use AS6C1008 as main RAM chip
2020-05-19 Add part SG7050 oscillator to the libraries
2020-05-19 Replace clock circuit by an encapsulated oscillator SG7050
2020-05-20 Add a symbol for TL7705 part
2020-05-20 Replace the custom power-on reset circuit by TL7705
2020-05-20 Add footprint for 1206 capacitors
2020-05-20 Add footprints for 1206 resistors
2020-05-20 Use ceramic capacitor for C15We actually have access to 1nF values in SMD encapsulation.
2020-05-21 Add code to generate GAL functions for decoding logic of model 201
2020-05-21 Add a symbol for GAL_declogic-201
2020-05-21 Add a footprint for SOIC 24p
2020-05-22 Add footprints for SOIC14, SOIC16 and SOIC20
2020-05-22 Use SOIC packages for remaining logic ICs that used DIP
2020-05-26 Add symbol 74HC670 to the library
2020-05-27 Remove jumper selectors for ROM image
2020-05-27 [mb201] Set JLCPCB PCB capabilities
2020-05-28 Fix wrong pinout of LM318
2020-05-31 [GFX9920] Include working output line for /CSYNC
2020-05-31 [GFX9920] Complete the first proposal of encoder circuit
2020-06-03 [gfx9920] Move G encoding resistors to clarify
2020-06-03 [gfx9920] Fix wrong values of resistors for green encoding
2020-06-05 [gfx9920] Fix wrong gain of blue encoding op-amp
2020-06-12 Fix the diagram to fit the successful experiments
2020-06-12 Adjust values to MAX4031 specs
2020-07-15 Set TAPR license to the project
2020-07-15 Add schematic circuit for power step up to 12V
2020-07-16 Add a emitter follower buffer for CSYNC
